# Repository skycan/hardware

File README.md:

hardware
========

Skycan hardware files.

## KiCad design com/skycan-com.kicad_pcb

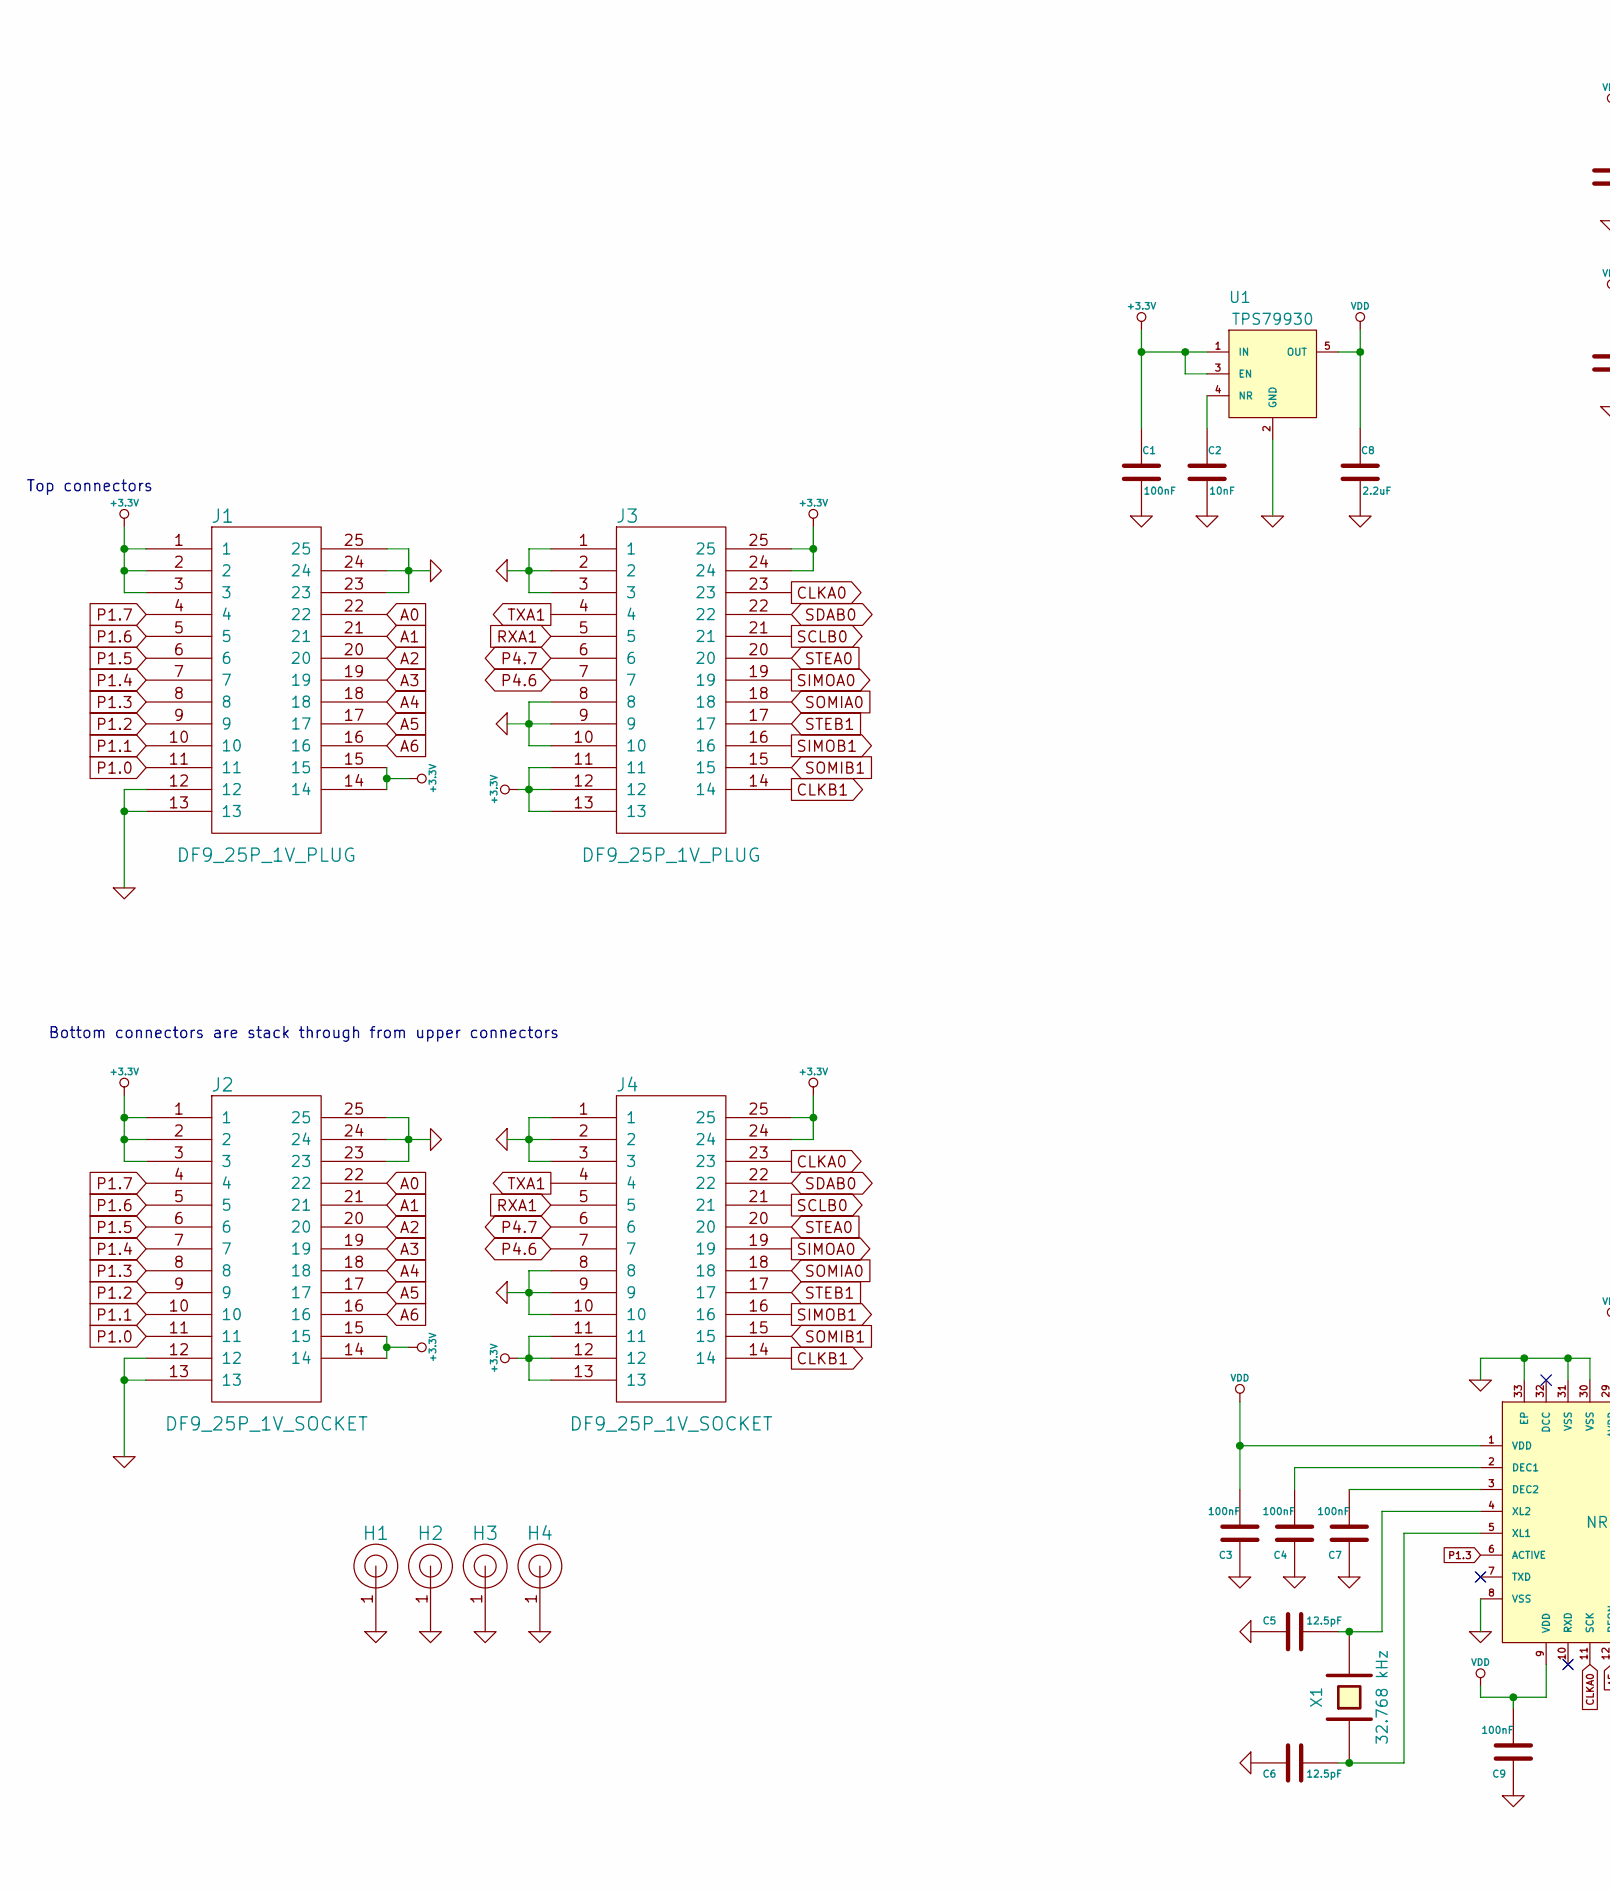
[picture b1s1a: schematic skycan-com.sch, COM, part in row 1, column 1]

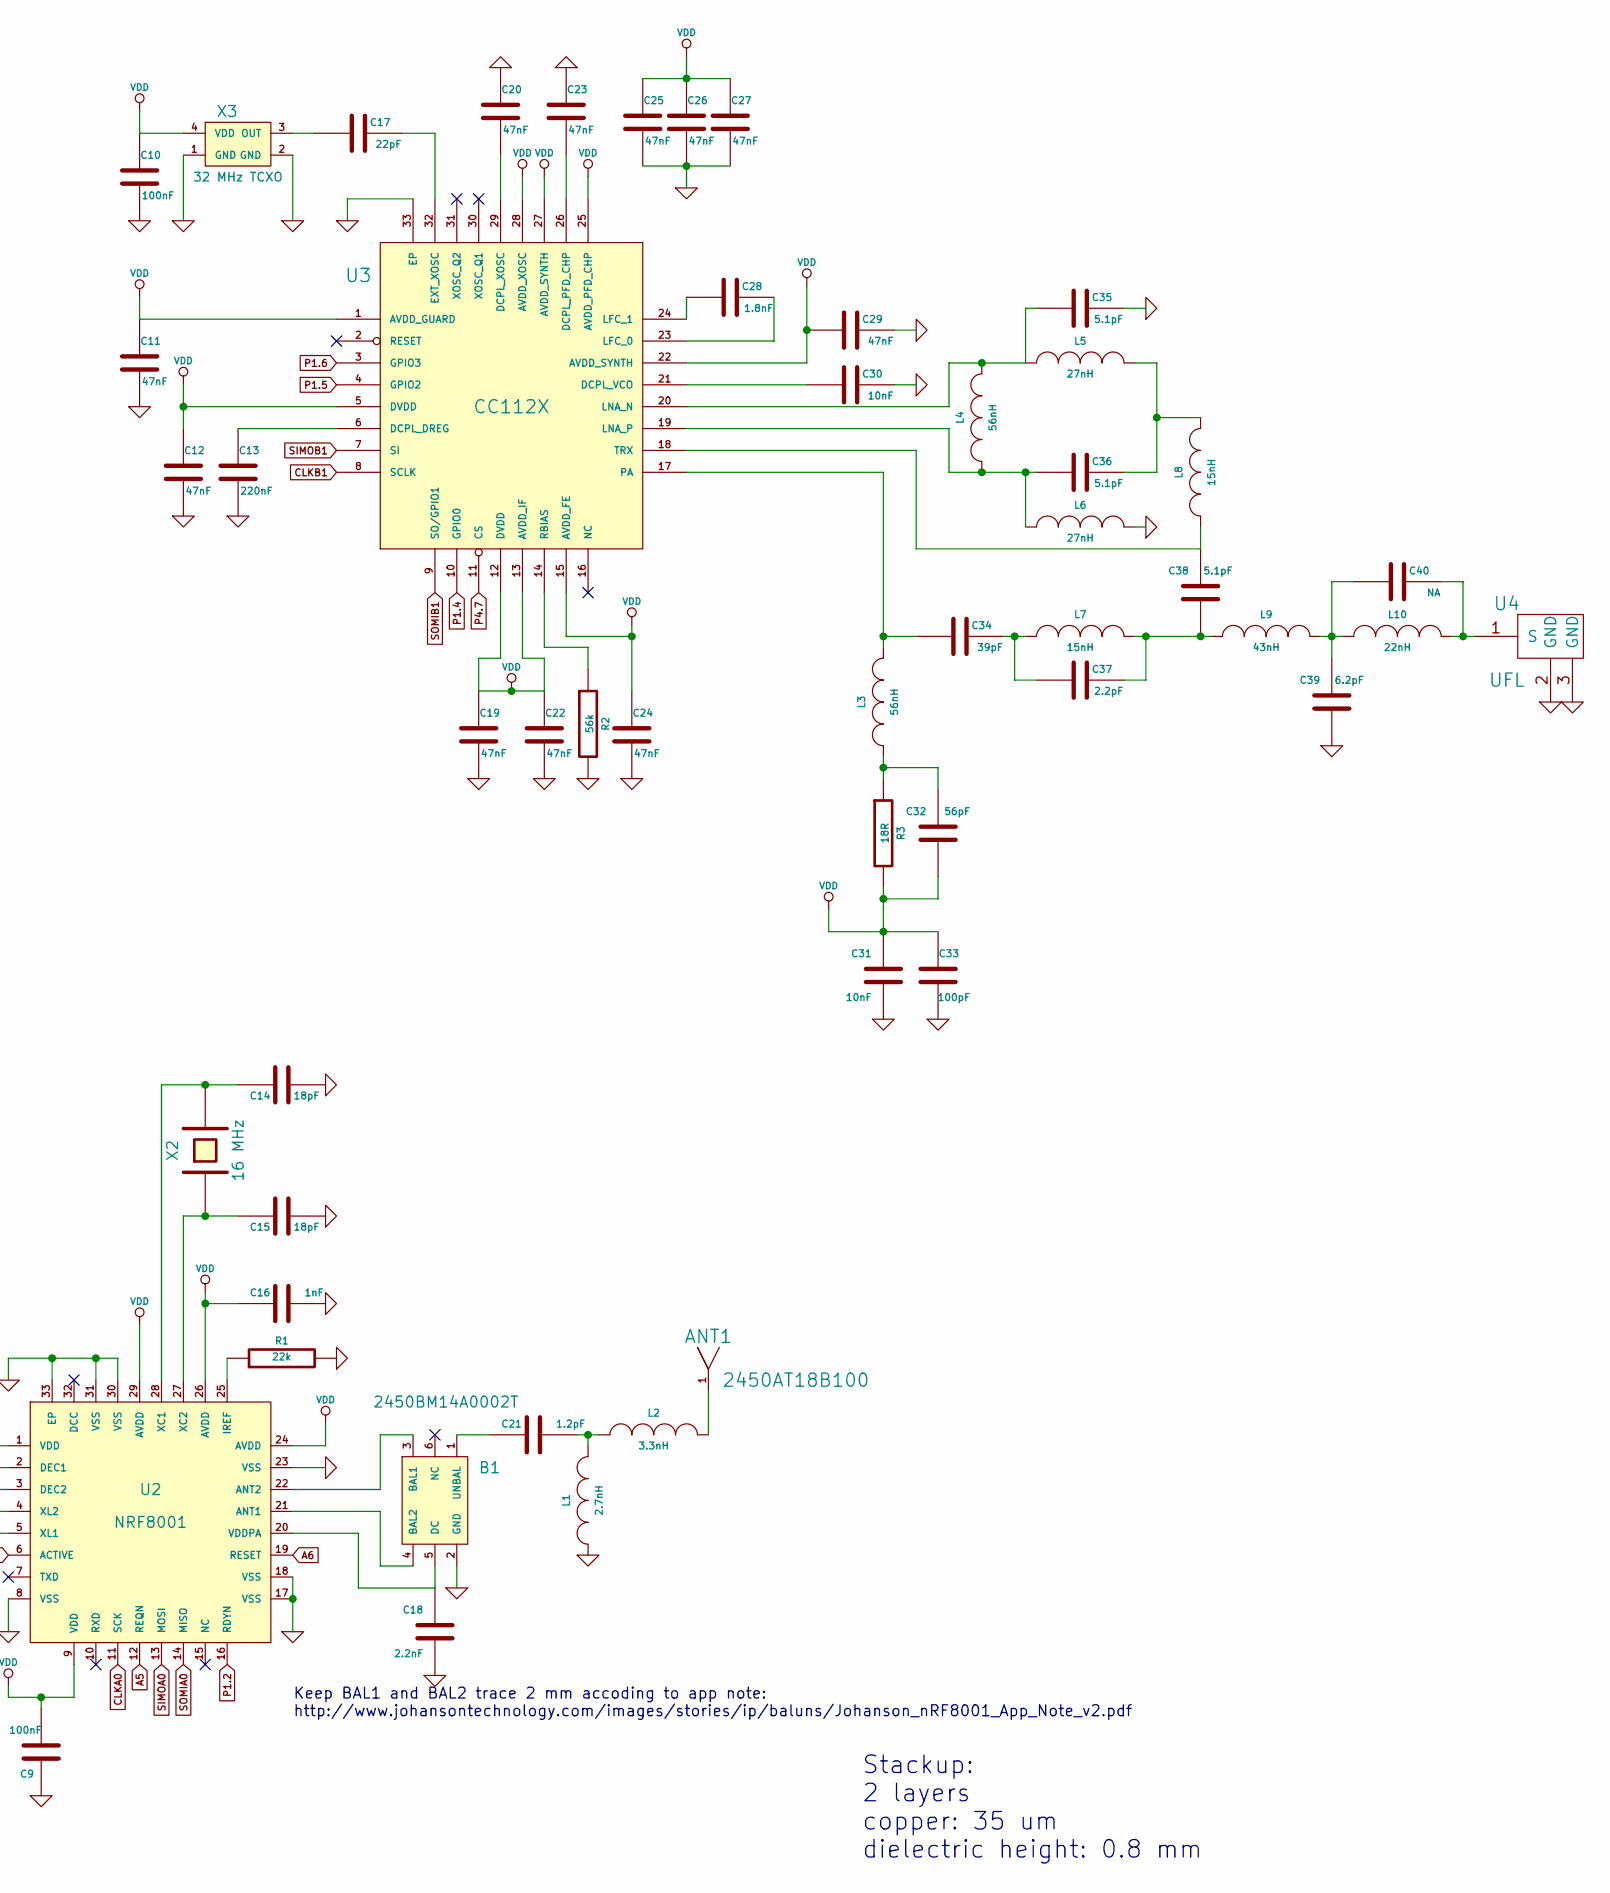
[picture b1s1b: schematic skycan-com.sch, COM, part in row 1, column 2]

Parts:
ANT1: 2450AT18B100; Farnell 1885497
B1: 2450BM14A0002T; Farnell 2148533
C1, C3, C4, C7, C9, C10: 100nF; 0402
C2, C30, C31: 10nF; 0402
C5, C6: 12.5pF; 0402
C8: 2.2uF; 0805
C11, C12, C19, C20, C22, C23, C24, C25, C26, C27, C29: 47nF; 0402
C13: 220nF; 0402
C14, C15: 18pF; 0402
C16: 1nF; 0402
C17: 22pF; 0402
C18: 2.2nF; 0402
C21: 1.2pF; 0402
C28: 1.8nF; 0402
C32: 56pF; 0402
C33: 100pF; 0402
C34: 39pF; 0402
C35, C36, C38: 5.1pF; 0402
C37: 2.2pF; 0402
C39: 6.2pF; 0402
C40: NA; 0402
H1, H2, H3, H4: HOLE
J1, J3: DF9_25P_1V_PLUG; Farnell 1798379
J2, J4: DF9_25P_1V_SOCKET; Farnell 1798380
L1: 2.7nH
L2: 3.3nH
L3, L4: 56nH
L5, L6: 27nH
L7, L8: 15nH
L9: 43nH
L10: 22nH
R1: 22k; 0402
R2: 56k; 0402
R3: 18R; 0402
U1: TPS79930; Farnell 1135402
U2: NRF8001; Mouser 949-NRF8001-R2Q32-T
U3: CC112X; Mouser 595-CC1120RHBT
U4: UFL; Farnell 1688077
X1: 32.768 kHz; Farnell 2101352
X2: 16 MHz; Farnell 1841946
X3: 32 MHz TCXO; Digikey WT325BI0032.000000CT-ND

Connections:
+3.3V: C1.1, J1.1, J1.2, J1.3, J1.14, J1.15, J2.1, J2.2, J2.3, J2.14, J2.15, J3.11, J3.12, J3.13, J3.24, J3.25, J4.11, J4.12, J4.13, J4.24, J4.25, U1.1 (IN), U1.3 (EN)
A0: J1.22, J2.22
A1: J1.21, J2.21
A2: J1.20, J2.20
A3: J1.19, J2.19
A4: J1.18, J2.18
A5: J1.17, J2.17, U2.12 (REQN)
A6: J1.16, J2.16, U2.19 (RESET)
CLKA0: J3.23, J4.23, U2.11 (SCK)
CLKB1: J3.14, J4.14, U3.8 (SCLK)
GND: B1.2 (GND), C1.2, C2.2, C3.2, C4.2, C5.2, C6.2, C7.2, C8.2, C9.2, C10.2, C11.2, C12.2, C13.2, C14.1, C15.1, C16.1, C18.1, C19.2, C20.1, C22.2, C23.1, C24.2, C25.2, C26.2, C27.2, C29.2, C30.2, C31.1, C33.1, C35.2, C39.1, H1.1, H2.1, H3.1, H4.1, J1.12, J1.13, J1.23, J1.24, J1.25, J2.12, J2.13, J2.23, J2.24, J2.25, J3.1, J3.2, J3.3, J3.8, J3.9, J3.10, J4.1, J4.2, J4.3, J4.8, J4.9, J4.10, L1.1, L6.2, R1.2, R2.2, U1.2 (GND), U2.8 (VSS), U2.17 (VSS), U2.18 (VSS), U2.23 (VSS), U2.30 (VSS), U2.31 (VSS), U2.33 (EP), U3.33 (EP), U4.2 (GND), U4.3 (GND), X3.1 (GND), X3.2 (GND)
unnamed: C36.2, L5.2, L8.2
unnamed: C38.2, L8.1, U3.18 (TRX)
unnamed: C34.2, C37.1, L7.1
unnamed: C17.2, U3.32 (EXT_XOSC)
unnamed: C17.1, X3.3 (OUT)
unnamed: C30.1, U3.21 (DCPL_VCO)
unnamed: C28.1, U3.24 (LFC_1)
unnamed: C28.2, U3.23 (LFC_0)
unnamed: C40.2, L10.2, U4.1 (S)
unnamed: C34.1, L3.2, U3.17 (PA)
unnamed: C39.2, C40.1, L9.2, L10.1
unnamed: C32.2, L3.1, R3.1
unnamed: R2.1, U3.14 (RBIAS)
unnamed: C13.1, U3.6 (DCPL_DREG)
unnamed: C23.2, U3.26 (DCPL_PFD_CHP)
unnamed: C20.2, U3.29 (DCPL_XOSC)
unnamed: C2.1, U1.4 (NR)
unnamed: C7.1, U2.3 (DEC2)
unnamed: C4.1, U2.2 (DEC1)
unnamed: C6.1, U2.5 (XL1), X1.1
unnamed: C5.1, U2.4 (XL2), X1.2
unnamed: B1.4 (BAL2), U2.21 (ANT1)
unnamed: B1.3 (BAL1), U2.22 (ANT2)
unnamed: B1.1 (UNBAL), C21.2
unnamed: ANT1.1, L2.2
unnamed: C21.1, L1.2, L2.1
unnamed: C14.2, U2.28 (XC1), X2.2
unnamed: R1.1, U2.25 (IREF)
unnamed: B1.5 (DC), C18.2, U2.20 (VDDPA)
unnamed: C15.2, U2.27 (XC2), X2.1
unnamed: C37.2, C38.1, L7.2, L9.1
unnamed: C36.1, L4.1, L6.1, U3.19 (LNA_P)
unnamed: C35.1, L4.2, L5.1, U3.20 (LNA_N)
P1.0: J1.11, J2.11
P1.1: J1.10, J2.10
P1.2: J1.9, J2.9, U2.16 (RDYN)
P1.3: J1.8, J2.8, U2.6 (ACTIVE)
P1.4: J1.7, J2.7, U3.10 (GPIO0)
P1.5: J1.6, J2.6, U3.4 (GPIO2)
P1.6: J1.5, J2.5, U3.3 (GPIO3)
P1.7: J1.4, J2.4
P4.6: J3.7, J4.7
P4.7: J3.6, J4.6, U3.11 (CS)
RXA1: J3.5, J4.5
SCLB0: J3.21, J4.21
SDAB0: J3.22, J4.22
SIMOA0: J3.19, J4.19, U2.13 (MOSI)
SIMOB1: J3.16, J4.16, U3.7 (SI)
SOMIA0: J3.18, J4.18, U2.14 (MISO)
SOMIB1: J3.15, J4.15, U3.9 (SO/GPIO1)
STEA0: J3.20, J4.20
STEB1: J3.17, J4.17
TXA1: J3.4, J4.4
VDD: C3.1, C8.1, C9.1, C10.1, C11.1, C12.1, C16.2, C19.1, C22.1, C24.1, C25.1, C26.1, C27.1, C29.1, C31.2, C32.1, C33.2, R3.2, U1.5 (OUT), U2.1 (VDD), U2.9 (VDD), U2.24 (AVDD), U2.26 (AVDD), U2.29 (AVDD), U3.1 (AVDD_GUARD), U3.5 (DVDD), U3.12 (DVDD), U3.13 (AVDD_IF), U3.15 (AVDD_FE), U3.22 (AVDD_SYNTH), U3.25 (AVDD_PFD_CHP), U3.27 (AVDD_SYNTH), U3.28 (AVDD_XOSC), X3.4 (VDD)

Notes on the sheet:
Top connectors
Bottom connectors are stack through from upper connectors
Stackup: 2 layers copper: 35 um dielectric height: 0.8 mm
Keep BAL1 and BAL2 trace 2 mm accoding to app note: http://www.johansontechnology.com/images/stories/ip/baluns/Johanson_nRF8001_App_Note_v2.pdf

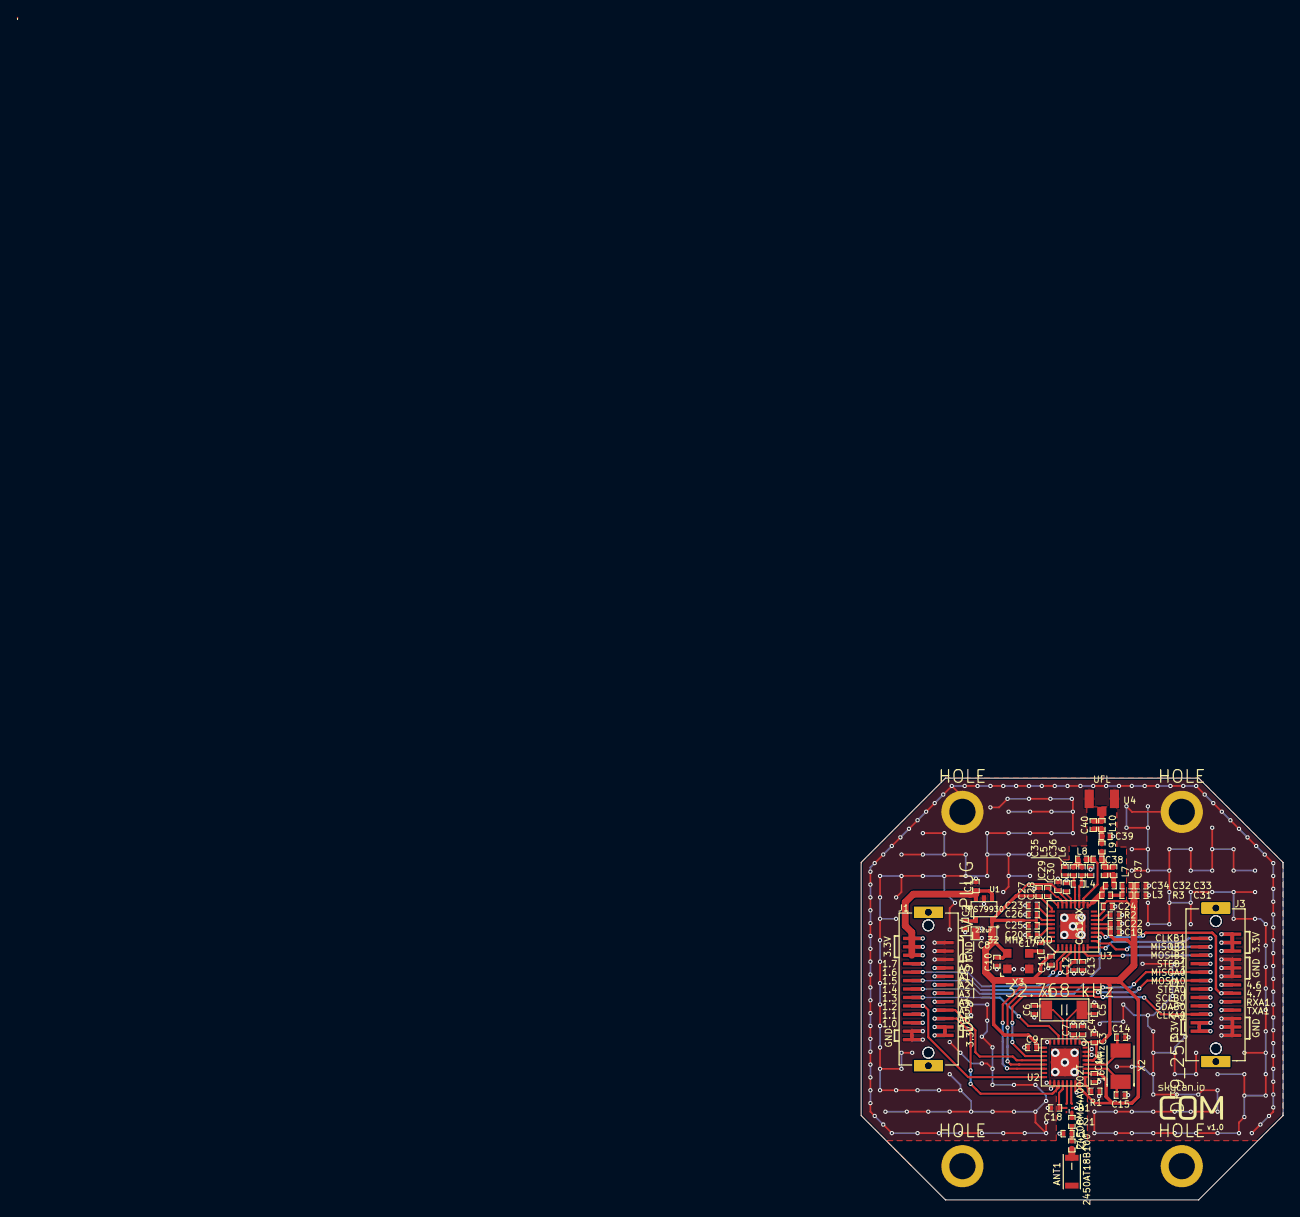
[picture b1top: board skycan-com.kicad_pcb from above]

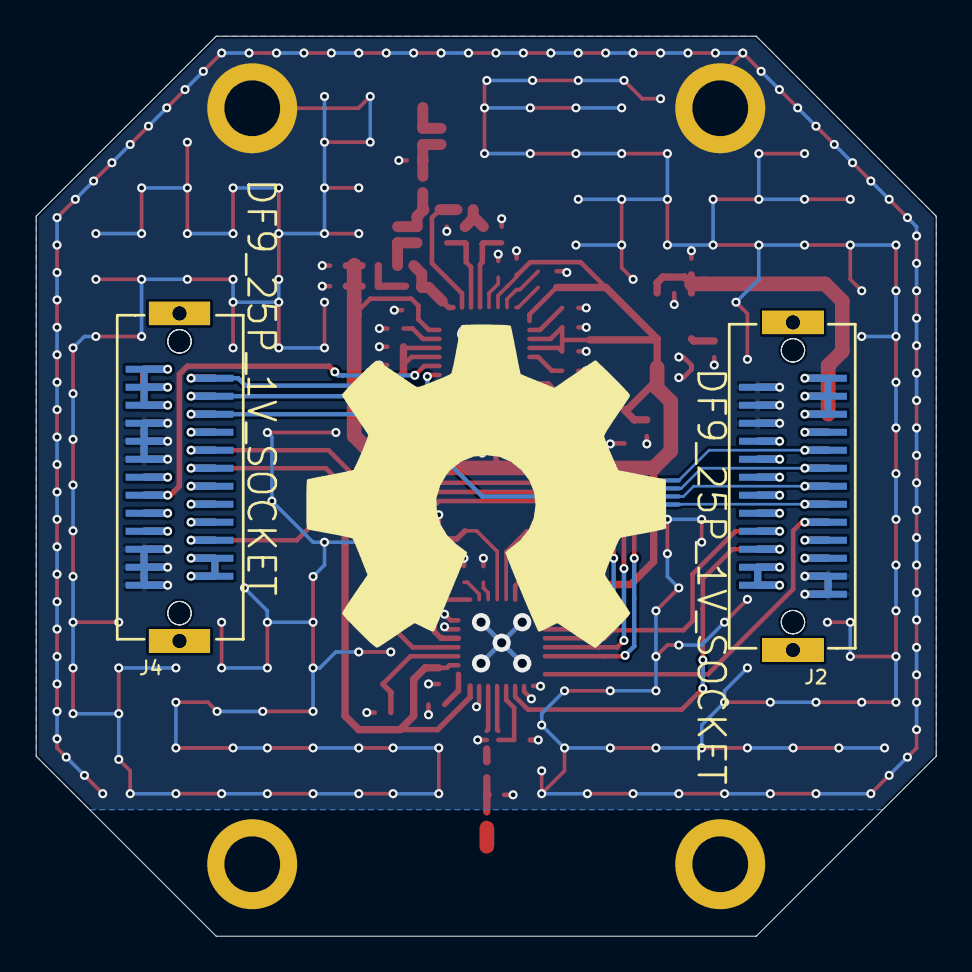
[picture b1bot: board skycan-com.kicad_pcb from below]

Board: 2 copper layers, 50.0 x 50.0 mm, 72 parts (2 on the bottom side), 65 nets.

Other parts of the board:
STUB: VAL**; STUB
VAL: skycan-com-logo

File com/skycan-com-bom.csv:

Reference,Value,LibPart,Footprint,Qty,Digikey,Farnell,Mouser
ANT1,2450AT18B100,skycan:2450AT18B100,,1,,1885497,
B1,2450BM14A0002T,skycan:2450BM14A0002T,,1,,2148533,
"C1, C10, C3, C4, C7, C9",100nF,device:C,0402,6,,,
"C11, C12, C19, C20, C22, C23, C24, C25, C26, C27, C29",47nF,device:C,0402,11,,,
C13,220nF,device:C,0402,1,,,
"C14, C15",18pF,device:C,0402,2,,,
C16,1nF,device:C,0402,1,,,
C17,22pF,device:C,0402,1,,,
C18,2.2nF,device:C,0402,1,,,
"C2, C30, C31",10nF,device:C,0402,3,,,
C21,1.2pF,device:C,0402,1,,,
C28,1.8nF,device:C,0402,1,,,
C32,56pF,device:C,0402,1,,,
C33,100pF,device:C,0402,1,,,
C34,39pF,device:C,0402,1,,,
"C35, C36, C38",5.1pF,device:C,0402,3,,,
C37,2.2pF,device:C,0402,1,,,
C39,6.2pF,device:C,0402,1,,,
C40,NA,device:C,0402,1,,,
"C5, C6",12.5pF,device:C,0402,2,,,
C8,2.2uF,device:C,0805,1,,,
"J1, J3",DF9_25P_1V_PLUG,skycan:DF9_25P_1V_PLUG,,2,,1798379,
"J2, J4",DF9_25P_1V_SOCKET,skycan:DF9_25P_1V_SOCKET,,2,,1798380,
L1,2.7nH,device:INDUCTOR_SMALL,,1,,,
L10,22nH,device:INDUCTOR_SMALL,,1,,,
L2,3.3nH,device:INDUCTOR_SMALL,,1,,,
"L3, L4",56nH,device:INDUCTOR_SMALL,,2,,,
"L5, L6",27nH,device:INDUCTOR_SMALL,,2,,,
"L7, L8",15nH,device:INDUCTOR_SMALL,,2,,,
L9,43nH,device:INDUCTOR_SMALL,,1,,,
R1,22k,device:R,0402,1,,,
R2,56k,device:R,0402,1,,,
R3,18R,device:R,0402,1,,,
U1,TPS79930,skycan:TPS79930,,1,,1135402,
U2,NRF8001,skycan:NRF8001,,1,,,949-NRF8001-R2Q32-T
U3,CC112X,skycan:CC112X,,1,,,595-CC1120RHBT
U4,UFL,skycan:UFL,,1,,1688077,
X1,32.768 kHz,device:CRYSTAL,,1,,2101352,
X2,16 MHz,device:CRYSTAL,,1,,1841946,
X3,32 MHz TCXO,skycan:WT325TCXO,,1,WT325BI0032.000000CT-ND,,

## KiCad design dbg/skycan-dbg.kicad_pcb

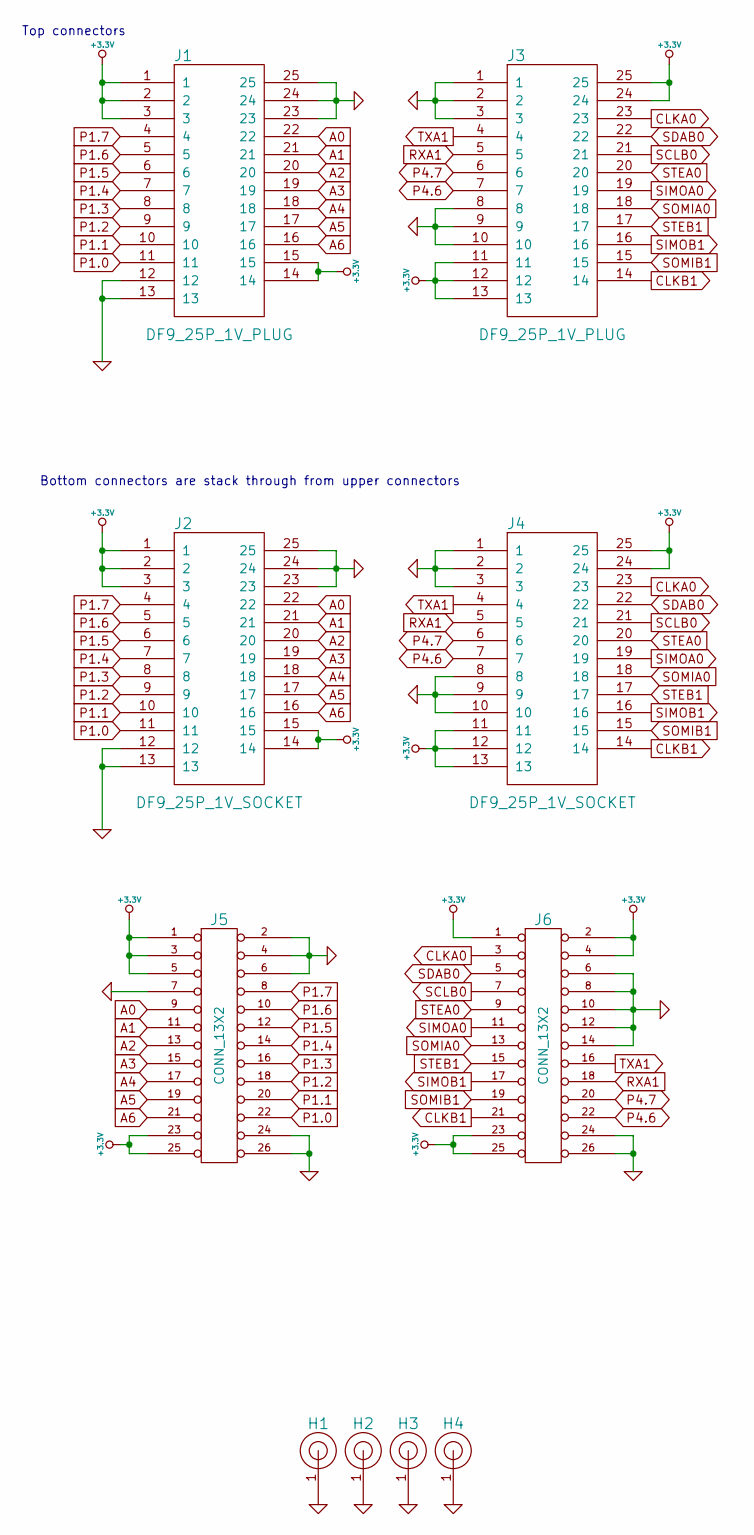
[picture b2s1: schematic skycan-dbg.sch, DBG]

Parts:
H1, H2, H3, H4: HOLE
J1, J3: DF9_25P_1V_PLUG; Farnell 1798379
J2, J4: DF9_25P_1V_SOCKET; Farnell 1798380
J5, J6: CONN_13X2

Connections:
+3.3V: J1.1, J1.2, J1.3, J1.14, J1.15, J2.1, J2.2, J2.3, J2.14, J2.15, J3.11, J3.12, J3.13, J3.24, J3.25, J4.11, J4.12, J4.13, J4.24, J4.25, J5.1, J5.3, J5.5, J5.23, J5.25 (P24), J6.1, J6.2, J6.4, J6.23, J6.25 (P24)
A0: J1.22, J2.22, J5.9
A1: J1.21, J2.21, J5.11
A2: J1.20, J2.20, J5.13
A3: J1.19, J2.19, J5.15
A4: J1.18, J2.18, J5.17
A5: J1.17, J2.17, J5.19
A6: J1.16, J2.16, J5.21
CLKA0: J3.23, J4.23, J6.3
CLKB1: J3.14, J4.14, J6.21
GND: H1.1, H2.1, H3.1, H4.1, J1.12, J1.13, J1.23, J1.24, J1.25, J2.12, J2.13, J2.23, J2.24, J2.25, J3.1, J3.2, J3.3, J3.8, J3.9, J3.10, J4.1, J4.2, J4.3, J4.8, J4.9, J4.10, J5.2, J5.4, J5.6, J5.7, J5.24 (P20), J5.26 (P22), J6.6, J6.8, J6.10, J6.12, J6.14, J6.24 (P20), J6.26 (P22)
P1.0: J1.11, J2.11, J5.22
P1.1: J1.10, J2.10, J5.20
P1.2: J1.9, J2.9, J5.18
P1.3: J1.8, J2.8, J5.16
P1.4: J1.7, J2.7, J5.14
P1.5: J1.6, J2.6, J5.12
P1.6: J1.5, J2.5, J5.10
P1.7: J1.4, J2.4, J5.8
P4.6: J3.7, J4.7, J6.22
P4.7: J3.6, J4.6, J6.20
RXA1: J3.5, J4.5, J6.18
SCLB0: J3.21, J4.21, J6.7
SDAB0: J3.22, J4.22, J6.5
SIMOA0: J3.19, J4.19, J6.11
SIMOB1: J3.16, J4.16, J6.17
SOMIA0: J3.18, J4.18, J6.13
SOMIB1: J3.15, J4.15, J6.19
STEA0: J3.20, J4.20, J6.9
STEB1: J3.17, J4.17, J6.15
TXA1: J3.4, J4.4, J6.16

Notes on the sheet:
Top connectors
Bottom connectors are stack through from upper connectors

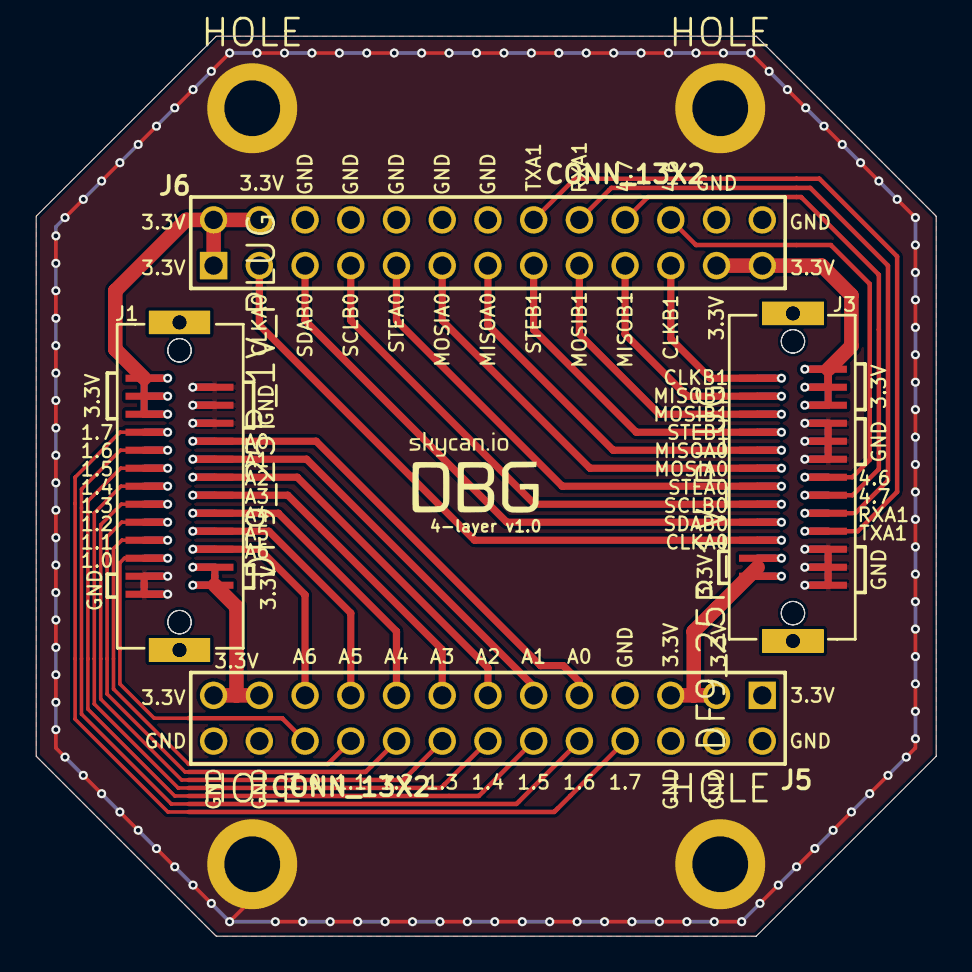
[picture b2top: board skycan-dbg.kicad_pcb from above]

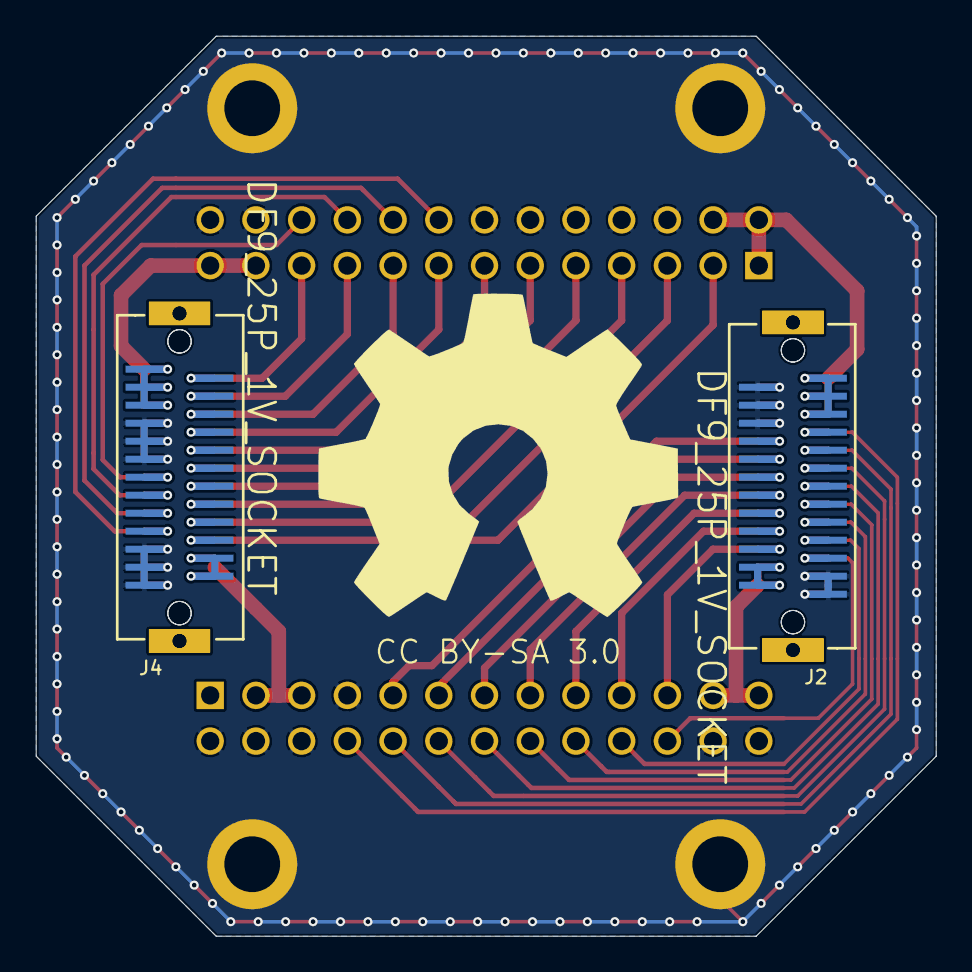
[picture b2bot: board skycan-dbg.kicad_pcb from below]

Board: 4 copper layers, 50.0 x 50.0 mm, 11 parts (2 on the bottom side), 31 nets.

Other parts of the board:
VAL: skycan-dbg-logo

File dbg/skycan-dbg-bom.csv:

Reference,Value,LibPart,Footprint,Qty,Farnell
"J1, J3",DF9_25P_1V_PLUG,skycan:DF9_25P_1V_PLUG,,2,1798379
"J2, J4",DF9_25P_1V_SOCKET,skycan:DF9_25P_1V_SOCKET,,2,1798380
"J5, J6",CONN_13X2,conn:CONN_13X2,,2,

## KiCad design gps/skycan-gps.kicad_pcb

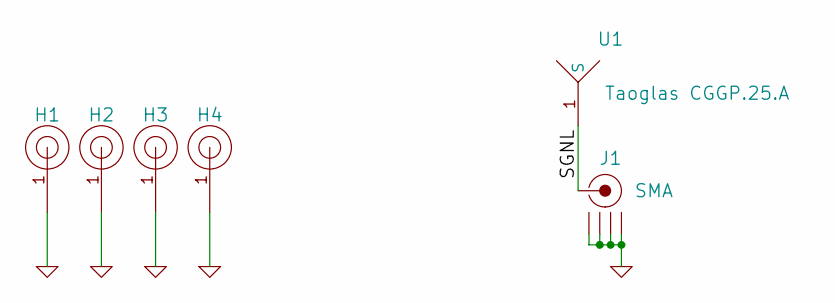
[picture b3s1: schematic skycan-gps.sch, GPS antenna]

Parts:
H1, H2, H3, H4: HOLE
J1: SMA; Farnell 1248990
U1: Taoglas CGGP.25.A; Mouser 960-CGGP254A02

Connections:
/SGNL: J1.1 (RF), U1.1
GND: H1.1, H2.1, H3.1, H4.1, J1.2 (GND1), J1.3 (GND2), J1.4 (GND3), J1.5 (GND4)

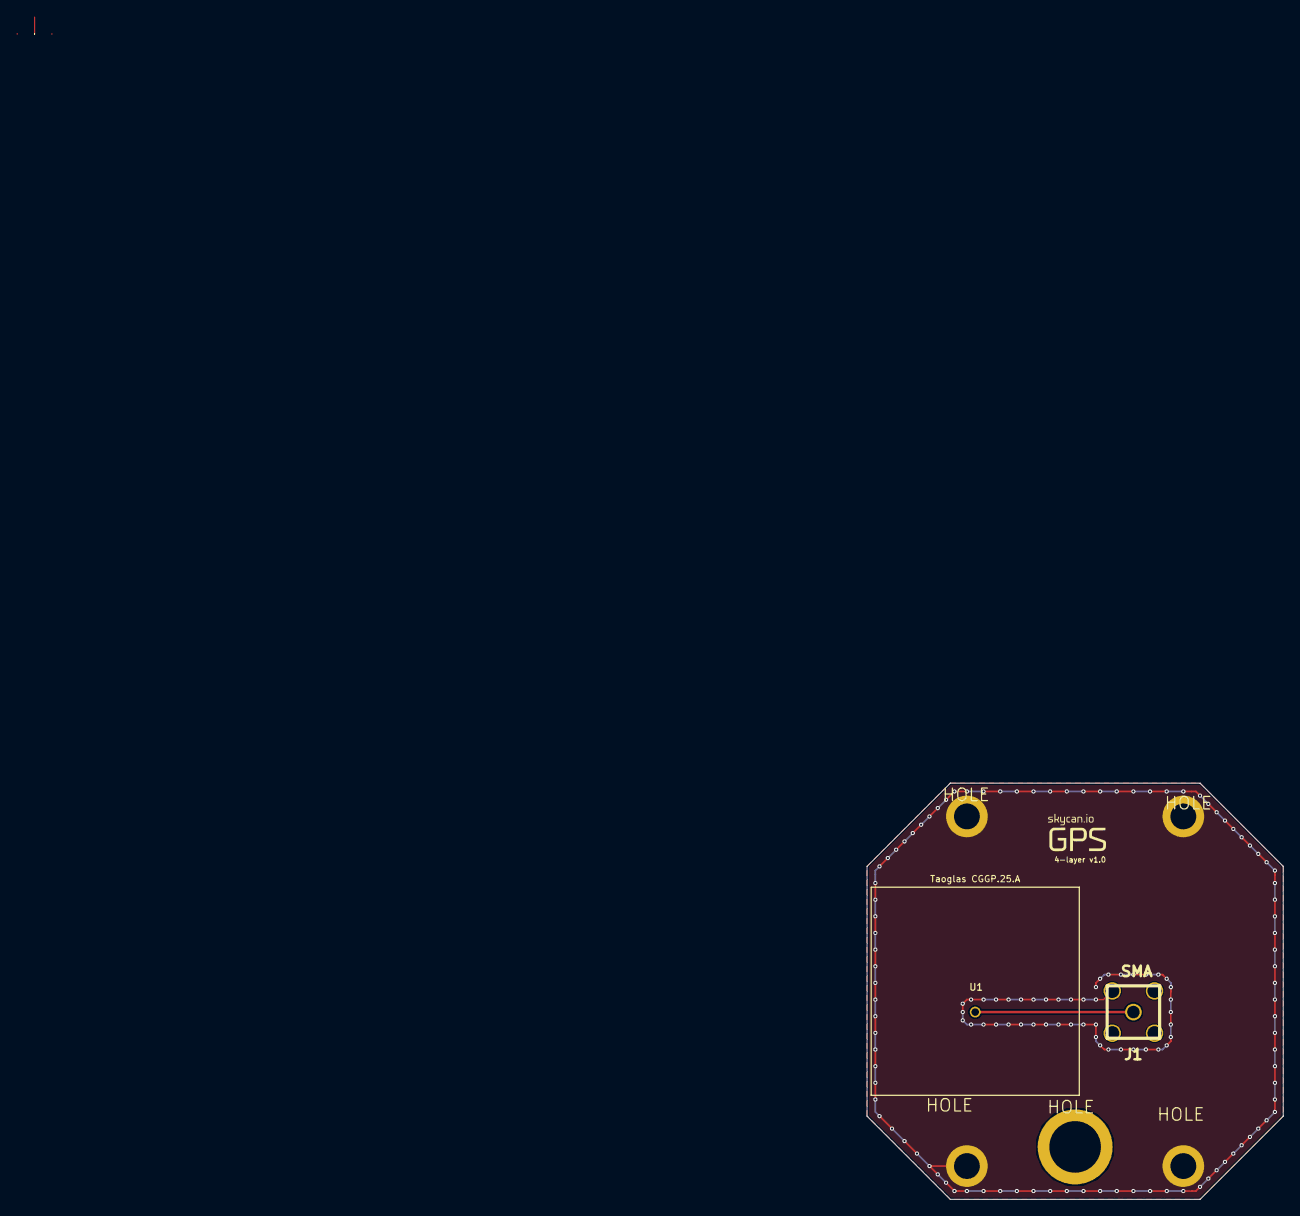
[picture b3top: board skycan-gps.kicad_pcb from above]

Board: 4 copper layers, 50.0 x 50.0 mm, 10 parts (0 on the bottom side), 2 nets.

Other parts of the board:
GAP: VAL**; GAP
H1#2: HOLE; mountinghole-6mm
STUB: VAL**; STUB
VAL: skycan-gps-logo

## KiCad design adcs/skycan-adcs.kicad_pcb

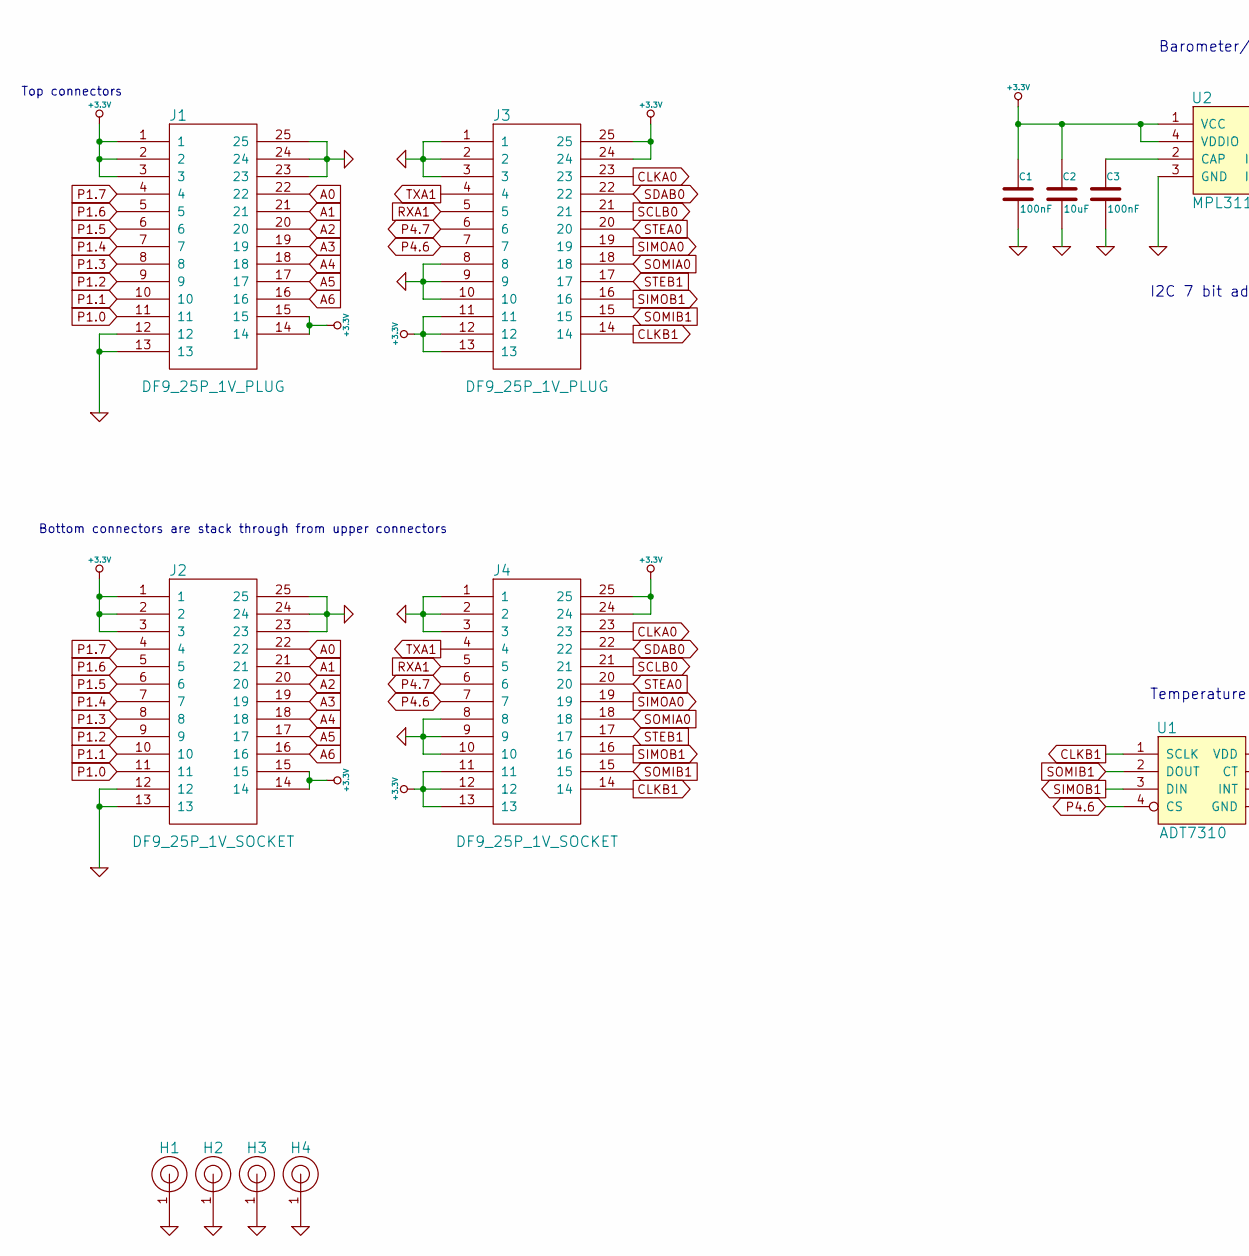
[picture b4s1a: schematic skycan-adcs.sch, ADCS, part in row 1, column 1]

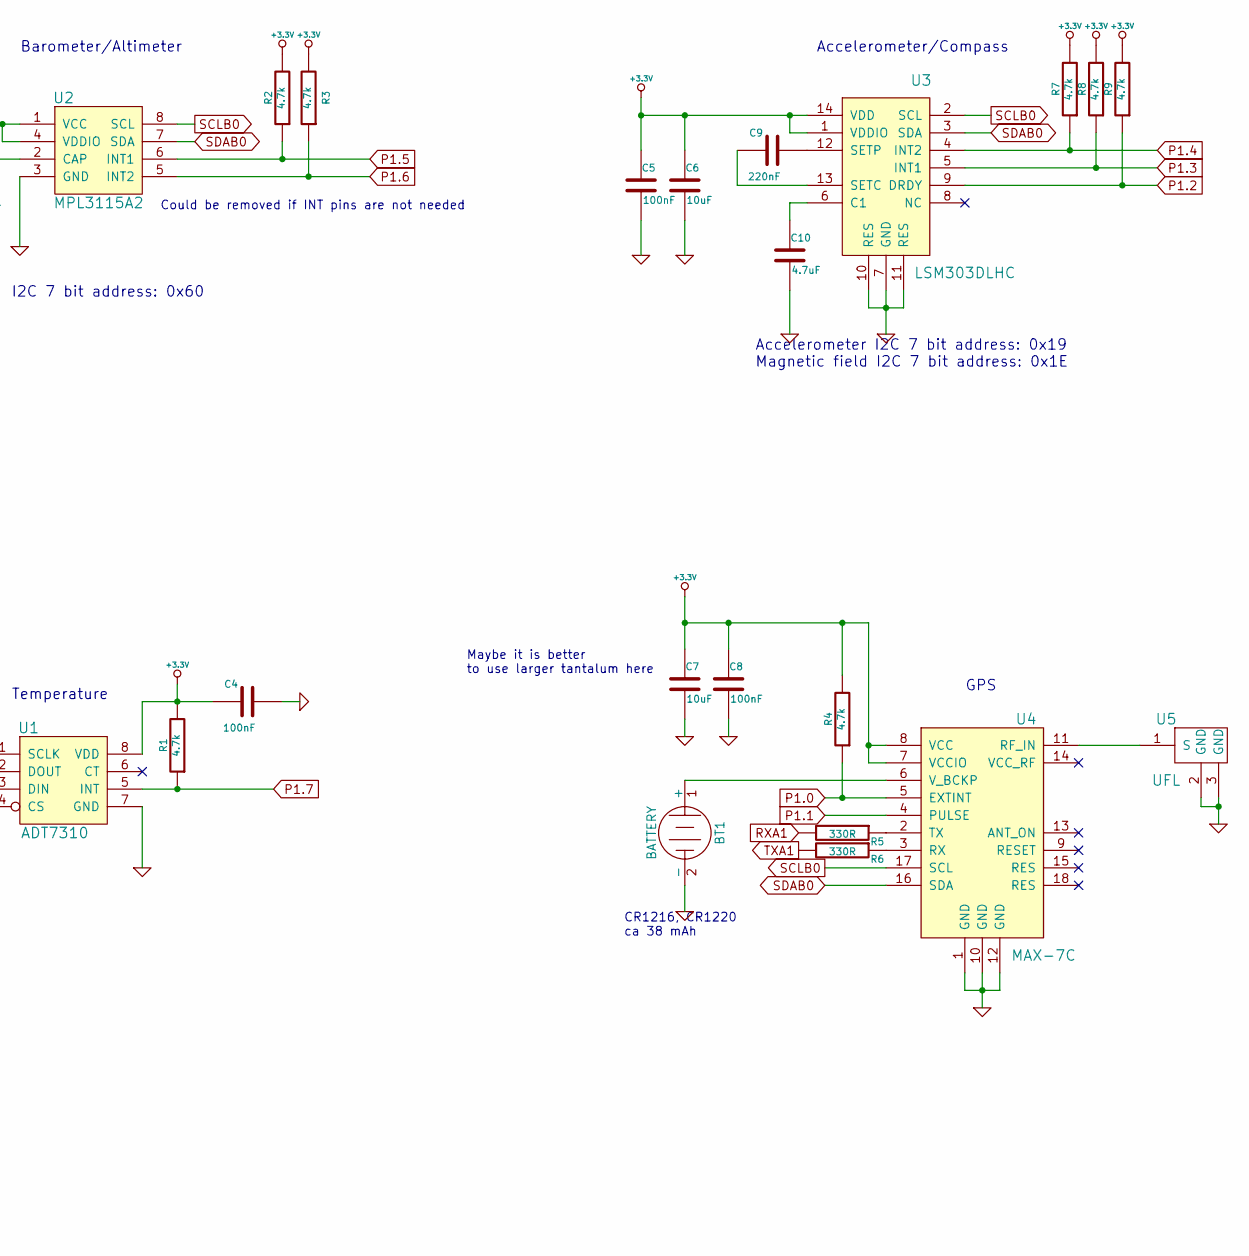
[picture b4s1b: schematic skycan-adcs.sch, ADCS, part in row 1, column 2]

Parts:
BT1: BATTERY; Farnell 908642
C1, C3, C4, C5, C8: 100nF; 0402
C2, C6: 10uF; 0603
C7: 10uF; 0805
C9: 220nF; 0402
C10: 4.7uF; 0603
H1, H2, H3, H4: HOLE
J1, J3: DF9_25P_1V_PLUG; Farnell 1798379
J2, J4: DF9_25P_1V_SOCKET; Farnell 1798380
R1, R2, R3, R4, R7, R8, R9: 4.7k
R5, R6: 330R
U1: ADT7310; SOIC8; Farnell 2067805
U2: MPL3115A2; LGA8; Farnell 2009084
U3: LSM303DLHC; LGA-14; Farnell 2068595
U4: MAX-7C
U5: UFL; Farnell 1688077

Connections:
+3.3V: C1.1, C2.1, C4.1, C5.1, C6.1, C7.1, C8.1, J1.1, J1.2, J1.3, J1.14, J1.15, J2.1, J2.2, J2.3, J2.14, J2.15, J3.11, J3.12, J3.13, J3.24, J3.25, J4.11, J4.12, J4.13, J4.24, J4.25, R1.2, R2.2, R3.2, R4.2, R7.2, R8.2, R9.2, U1.8 (VDD), U2.1 (VCC), U2.4 (VDDIO), U3.1 (VDDIO), U3.14 (VDD), U4.7 (VCCIO), U4.8 (VCC)
A0: J1.22, J2.22
A1: J1.21, J2.21
A2: J1.20, J2.20
A3: J1.19, J2.19
A4: J1.18, J2.18
A5: J1.17, J2.17
A6: J1.16, J2.16
CLKA0: J3.23, J4.23
CLKB1: J3.14, J4.14, U1.1 (SCLK)
GND: BT1.2 (-), C1.2, C2.2, C3.2, C4.2, C5.2, C6.2, C7.2, C8.2, C10.2, H1.1, H2.1, H3.1, H4.1, J1.12, J1.13, J1.23, J1.24, J1.25, J2.12, J2.13, J2.23, J2.24, J2.25, J3.1, J3.2, J3.3, J3.8, J3.9, J3.10, J4.1, J4.2, J4.3, J4.8, J4.9, J4.10, U1.7 (GND), U2.3 (GND), U3.7 (GND), U3.10 (RES), U3.11 (RES), U4.1 (GND), U4.10 (GND), U4.12 (GND), U5.2 (GND), U5.3 (GND)
unnamed: R5.1, U4.2 (TX)
unnamed: R6.1, U4.3 (RX)
unnamed: U4.11 (RF_IN), U5.1 (S)
unnamed: BT1.1 (+), U4.6 (V_BCKP)
unnamed: C9.1, U3.13 (SETC)
unnamed: C10.1, U3.6 (C1)
unnamed: C3.1, U2.2 (CAP)
unnamed: C9.2, U3.12 (SETP)
P1.0: J1.11, J2.11, R4.1, U4.5 (EXTINT)
P1.1: J1.10, J2.10, U4.4 (PULSE)
P1.2: J1.9, J2.9, R9.1, U3.9 (DRDY)
P1.3: J1.8, J2.8, R8.1, U3.5 (INT1)
P1.4: J1.7, J2.7, R7.1, U3.4 (INT2)
P1.5: J1.6, J2.6, R2.1, U2.6 (INT1)
P1.6: J1.5, J2.5, R3.1, U2.5 (INT2)
P1.7: J1.4, J2.4, R1.1, U1.5 (INT)
P4.6: J3.7, J4.7, U1.4 (CS)
P4.7: J3.6, J4.6
RXA1: J3.5, J4.5, R5.2
SCLB0: J3.21, J4.21, U2.8 (SCL), U3.2 (SCL), U4.17 (SCL)
SDAB0: J3.22, J4.22, U2.7 (SDA), U3.3 (SDA), U4.16 (SDA)
SIMOA0: J3.19, J4.19
SIMOB1: J3.16, J4.16, U1.3 (DIN)
SOMIA0: J3.18, J4.18
SOMIB1: J3.15, J4.15, U1.2 (DOUT)
STEA0: J3.20, J4.20
STEB1: J3.17, J4.17
TXA1: J3.4, J4.4, R6.2

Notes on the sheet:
Top connectors
Bottom connectors are stack through from upper connectors
Barometer/Altimeter
I2C 7 bit address: 0x60
Could be removed if INT pins are not needed
Accelerometer/Compass
Accelerometer I2C 7 bit address: 0x19 Magnetic field I2C 7 bit address: 0x1E
Temperature
GPS
Maybe it is better to use larger tantalum here
CR1216, CR1220 ca 38 mAh

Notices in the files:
adcs/skycan-adcs.kicad_pcb:
CC BY-SA 3.0
